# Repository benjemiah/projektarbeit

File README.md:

# projektarbeit

Git-Repo für die Projektarbeit des 6. Semesters

## Struktur

- **pcb**: KiCad-Projektdateien für die Platine des Retro-Terminals
  - **Gerber**: Gerber-Files der Platine
  - **eigenes.pretty**: Nicht-Standard Footprints/ Schaltzeichen für Bauteile
- **code**: Arduino-Code für die Atmega328P's des Retro-Terminals
- **presentation**
  - **website**: Website zur Präsentation des Projektseminars

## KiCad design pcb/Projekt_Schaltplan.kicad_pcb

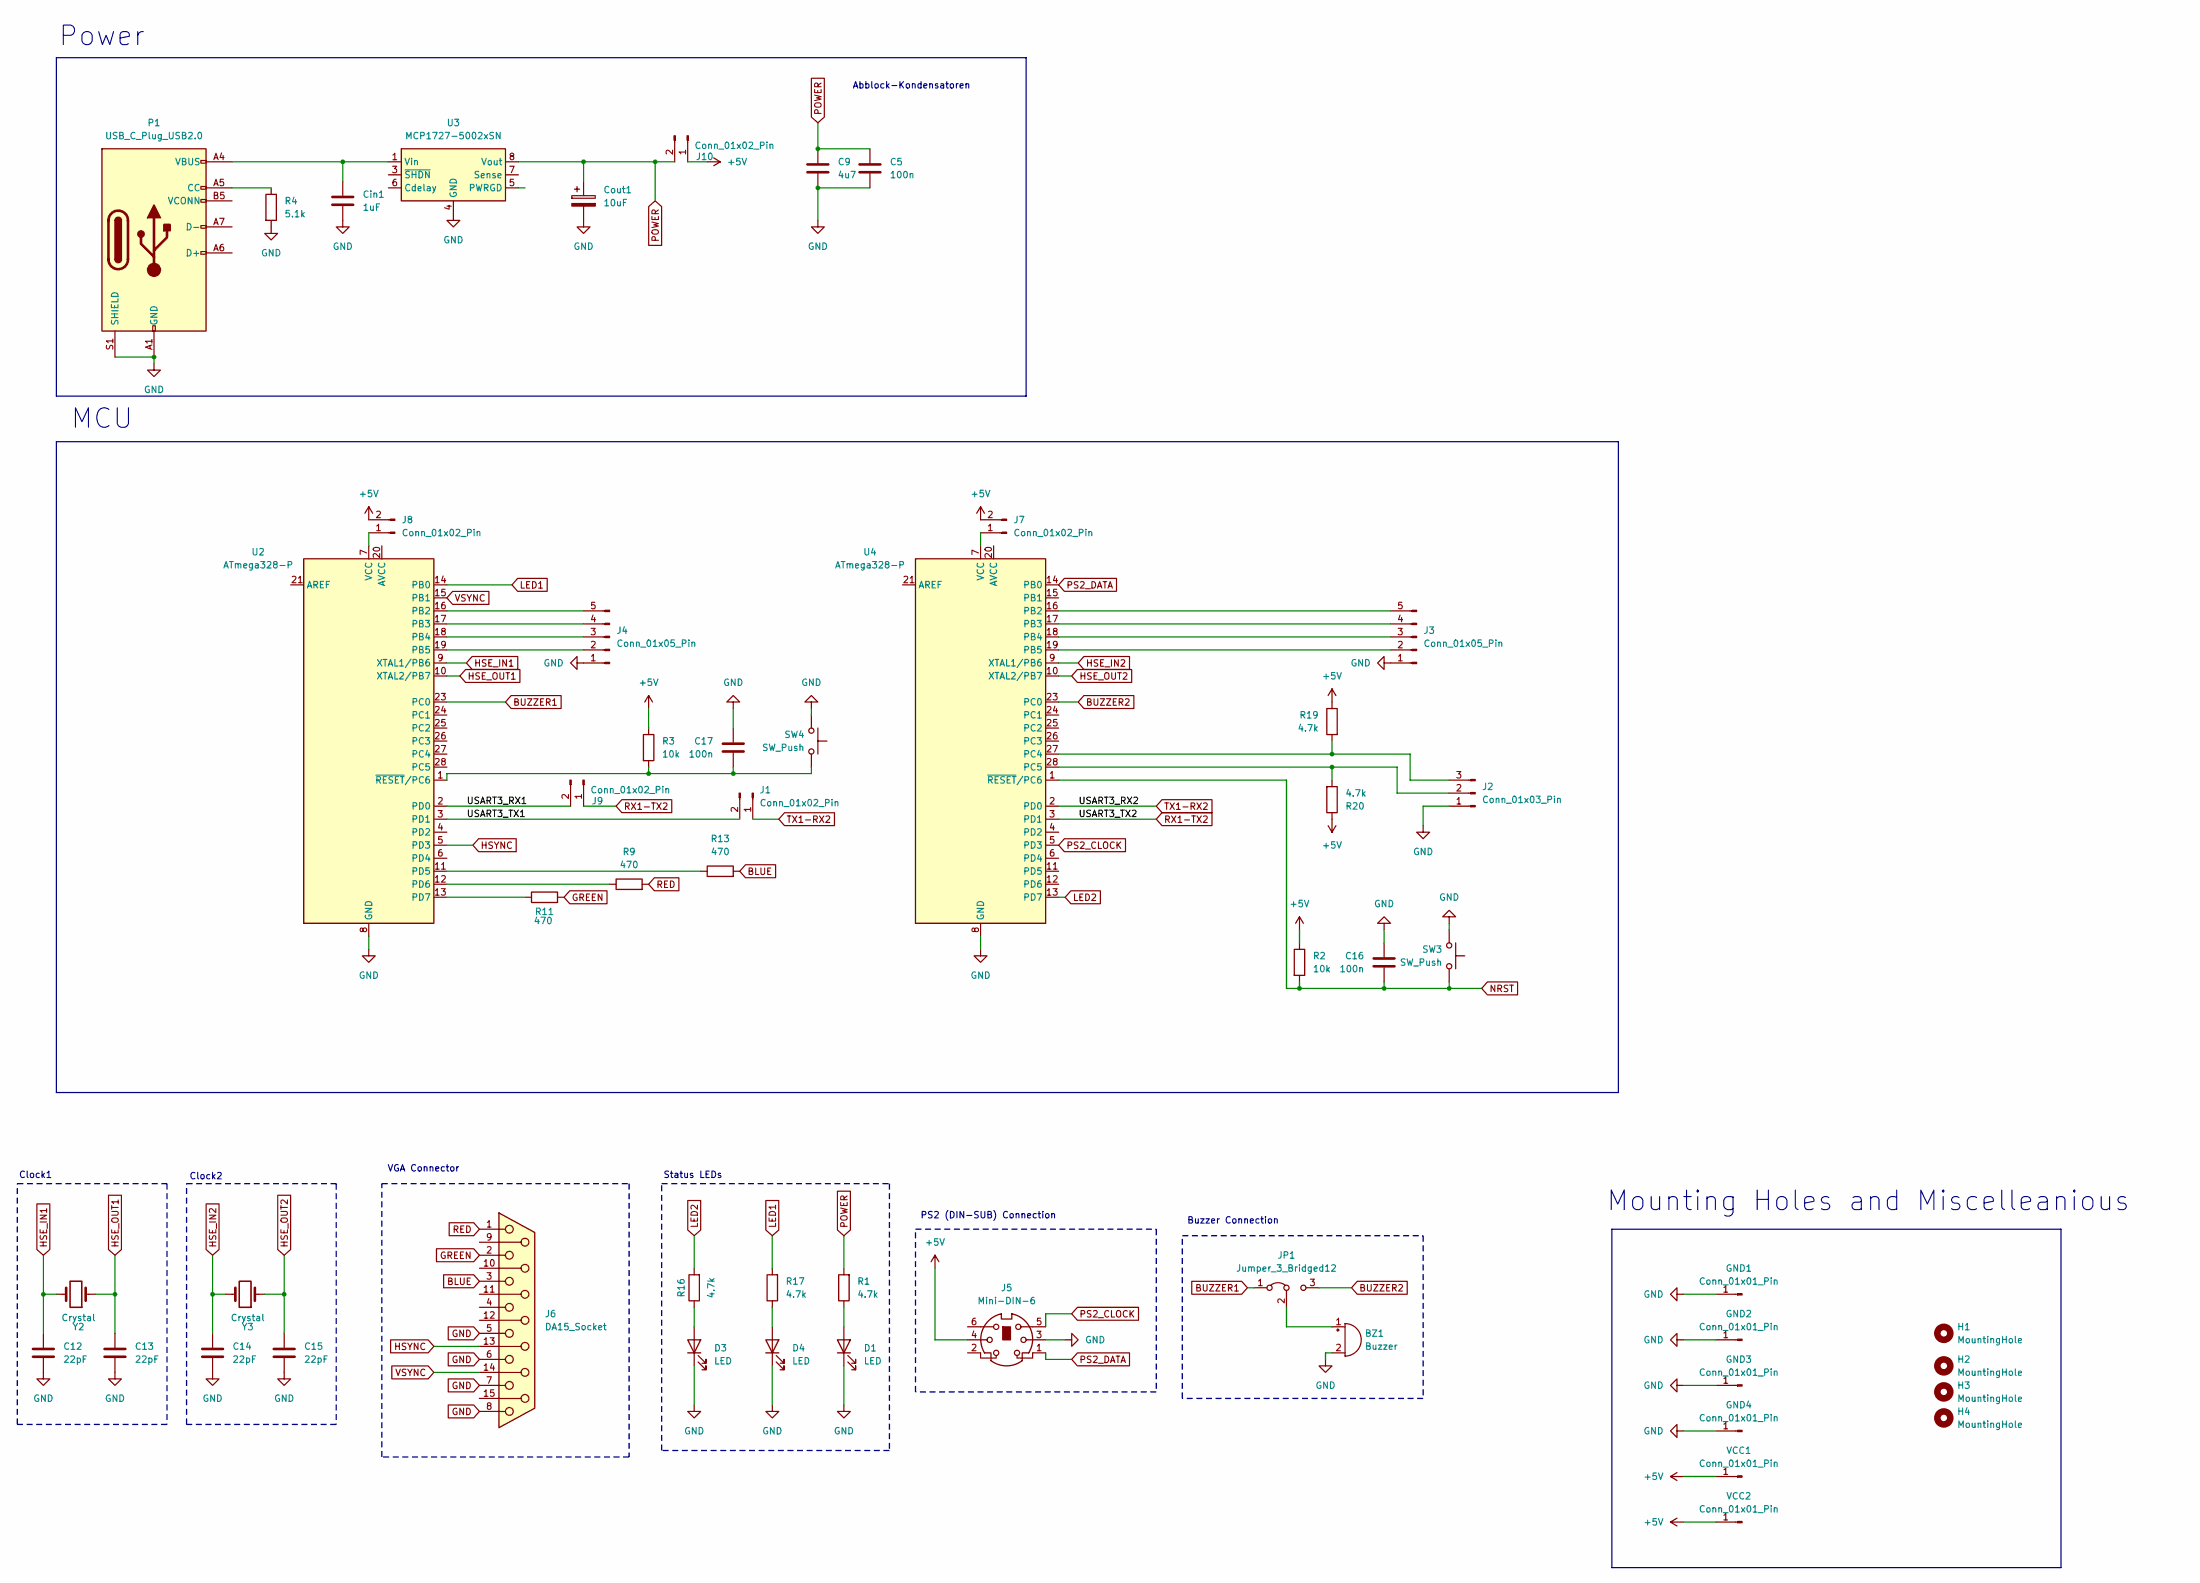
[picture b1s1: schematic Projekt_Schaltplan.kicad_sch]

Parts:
BZ1: Buzzer; Buzzer_12x9.5RM7.6
C5: 100n; C_0805_2012Metric_Pad1.18x1.45mm_HandSolder
C9: 4u7; C_0805_2012Metric_Pad1.18x1.45mm_HandSolder
C12, C13, C14, C15: 22pF; C_0805_2012Metric_Pad1.18x1.45mm_HandSolder
C16, C17: 100n; C_0603_1608Metric_Pad1.08x0.95mm_HandSolder
Cin1: 1uF; C_0805_2012Metric_Pad1.18x1.45mm_HandSolder
Cout1: 10uF; C_0805_2012Metric_Pad1.18x1.45mm_HandSolder
D1, D3, D4: LED; LED_0805_2012Metric_Pad1.15x1.40mm_HandSolder
GND1, GND2, GND3, GND4: Conn_01x01_Pin; TestPoint_THTPad_D2.0mm_Drill1.0mm
H1, H2, H3, H4: MountingHole; MountingHole_3.2mm_M3_DIN965_Pad
J1, J7, J8, J9, J10: Conn_01x02_Pin; PinHeader_1x02_P2.54mm_Vertical
J2: Conn_01x03_Pin; PinHeader_1x03_P2.54mm_Vertical
J3, J4: Conn_01x05_Pin; PinHeader_1x05_P2.54mm_Vertical
J5: Mini-DIN-6; ps2-buchse-6pin
J6: DA15_Socket; DSUB-15-HD_Socket_Vertical_P2.29x1.98mm_MountingHoles
JP1: Jumper_3_Bridged12; PinHeader_1x03_P2.54mm_Vertical
P1: USB_C_Plug_USB2.0; USB_C_Receptacle_GCT_USB4105-xx-A_16P_TopMnt_Horizontal
R1, R16, R17, R19, R20: 4.7k; R_0805_2012Metric_Pad1.20x1.40mm_HandSolder
R2, R3: 10k; R_0805_2012Metric_Pad1.20x1.40mm_HandSolder
R4: 5.1k; R_0805_2012Metric_Pad1.20x1.40mm_HandSolder
R9, R11, R13: 470; R_0805_2012Metric_Pad1.20x1.40mm_HandSolder
SW3, SW4: SW_Push; SW_PUSH_6mm
U2, U4: ATmega328-P; DIP-28_W7.62mm_Socket
U3: MCP1727-5002xSN; SOIC-8_3.9x4.9mm_P1.27mm
VCC1, VCC2: Conn_01x01_Pin; TestPoint_THTPad_D2.0mm_Drill1.0mm
Y2, Y3: Crystal; Crystal_HC49-U_Vertical

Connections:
+5V: J5.4, J7.2, J8.2, J10.1, R2.1, R3.1, R19.1, R20.1, VCC1.1, VCC2.1
/USART3_RX1: J9.2, U2.2 (PD0)
/USART3_TX1: J1.2, U2.3 (PD1)
BLUE: J6.3, R13.2
BUZZER1: JP1.1 (A), U2.23 (PC0)
BUZZER2: JP1.3 (B), U4.23 (PC0)
GND: BZ1.2 (-), C5.2, C9.2, C12.2, C13.2, C14.2, C15.2, C16.1, C17.1, Cin1.2, Cout1.2, D1.1 (K), D3.1 (K), D4.1 (K), GND1.1, GND2.1, GND3.1, GND4.1, J2.1, J3.1, J4.1, J5.3, J6.5, J6.6, J6.7, J6.8, P1.A1 (GND), P1.A12 (GND), P1.B1 (GND), P1.B12 (GND), P1.S1 (SHIELD), R4.2, SW3.2, SW4.2, U2.8 (GND), U2.22 (GND), U3.4 (GND), U4.8 (GND), U4.22 (GND)
GREEN: J6.2, R11.2
HSE_IN1: C12.1, U2.9 (XTAL1/PB6), Y2.2
HSE_IN2: C14.1, U4.9 (XTAL1/PB6), Y3.2
HSE_OUT1: C13.1, U2.10 (XTAL2/PB7), Y2.1
HSE_OUT2: C15.1, U4.10 (XTAL2/PB7), Y3.1
HSYNC: J6.13, U2.5 (PD3)
LED1: R17.2, U2.14 (PB0)
LED2: R16.2, U4.13 (PD7)
NRST: C16.2, R2.2, SW3.1, U4.1 (~RESET/PC6)
unnamed: BZ1.1 (+), JP1.2 (C)
unnamed: Cin1.1, P1.A4 (VBUS), P1.A9 (VBUS), P1.B4 (VBUS), P1.B9 (VBUS), U3.1 (Vin), U3.2 (Vin)
unnamed: D1.2 (A), R1.1
unnamed: D3.2 (A), R16.1
unnamed: D4.2 (A), R17.1
unnamed: J2.2, R20.2, U4.28 (PC5)
unnamed: J2.3, R19.2, U4.27 (PC4)
unnamed: J3.2, U4.19 (PB5)
unnamed: J3.3, U4.18 (PB4)
unnamed: J3.4, U4.17 (PB3)
unnamed: J3.5, U4.16 (PB2)
unnamed: J4.2, U2.19 (PB5)
unnamed: J4.3, U2.18 (PB4)
unnamed: J4.4, U2.17 (PB3)
unnamed: J4.5, U2.16 (PB2)
unnamed: J7.1, U4.7 (VCC)
unnamed: J8.1, U2.7 (VCC)
unnamed: P1.A5 (CC), R4.1
unnamed: R13.1, U2.11 (PD5)
unnamed: R9.1, U2.12 (PD6)
unnamed: R11.1, U2.13 (PD7)
unnamed: C17.2, R3.2, SW4.1, U2.1 (~RESET/PC6)
POWER: C5.1, C9.1, Cout1.1, J10.2, R1.2, U3.8 (Vout)
PS2_CLOCK: J5.5, U4.5 (PD3)
PS2_DATA: J5.1, U4.14 (PB0)
RED: J6.1, R9.2
RX1-TX2: J9.1, U4.3 (PD1)
TX1-RX2: J1.1, U4.2 (PD0)
VSYNC: J6.14, U2.15 (PB1)

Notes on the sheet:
Power
Clock1
PS2 (DIN-SUB) Connection
Clock2
Abblock-Kondensatoren
Buzzer Connection
MCU
Mounting Holes and Miscelleanious
Status LEDs
VGA Connector

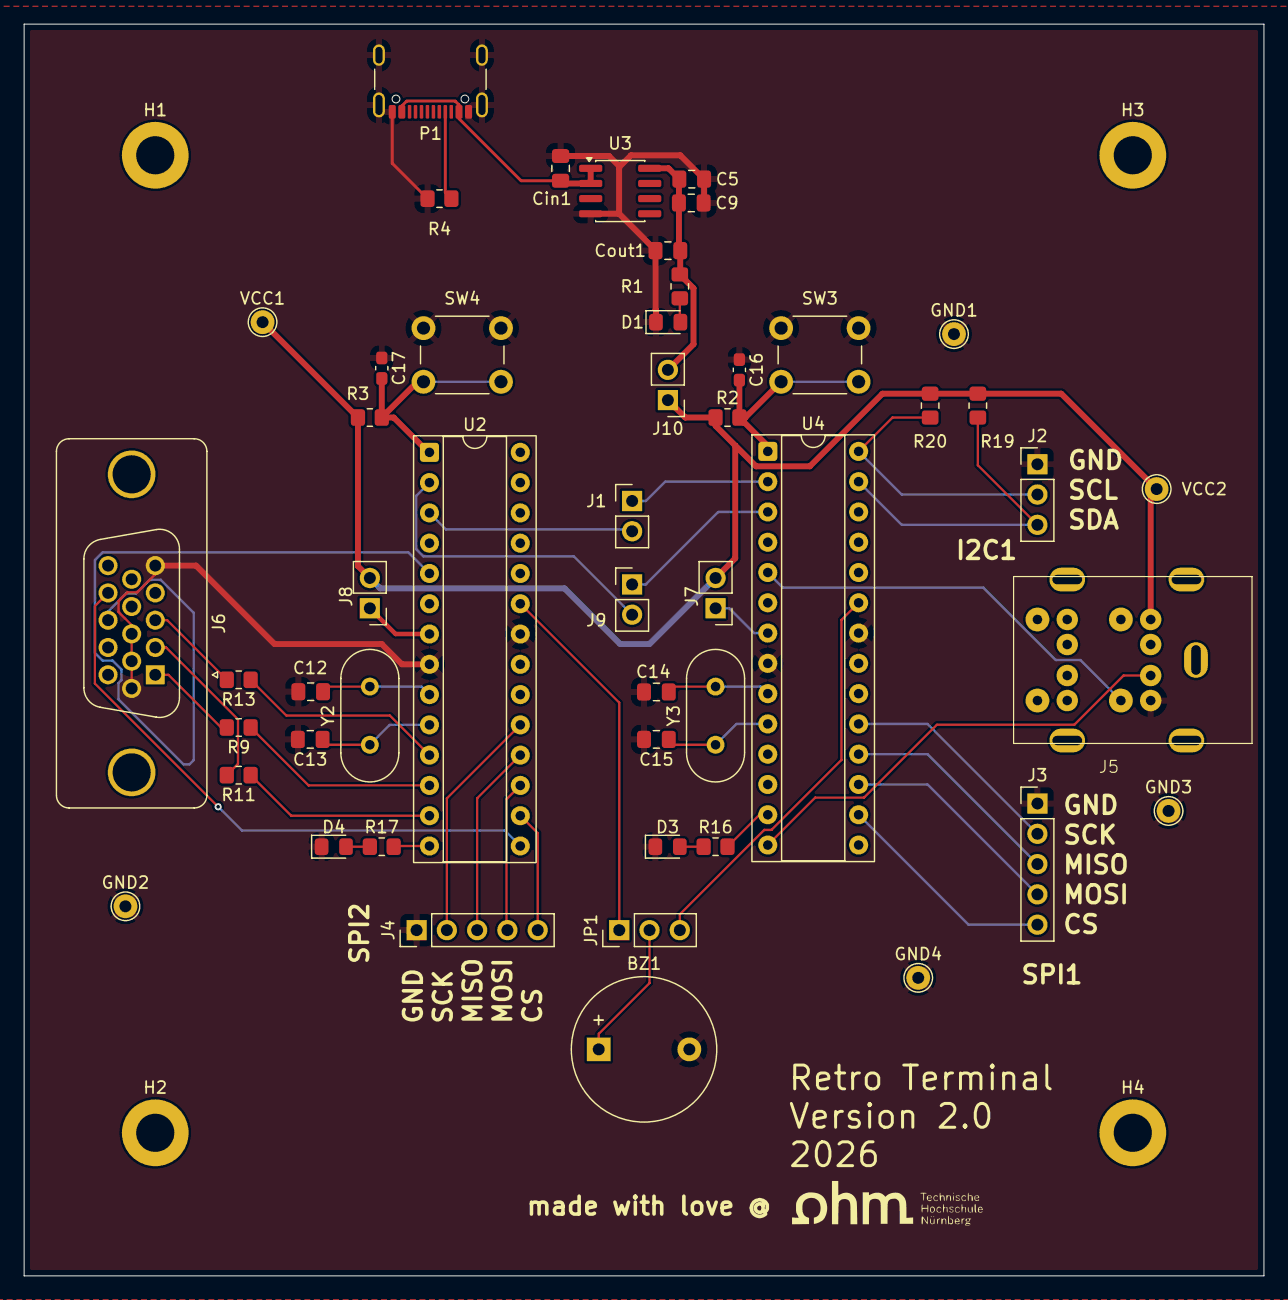
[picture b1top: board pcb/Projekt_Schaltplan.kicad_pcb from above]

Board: 2 copper layers, 104.0 x 105.0 mm, 54 parts (0 on the bottom side), 45 nets.

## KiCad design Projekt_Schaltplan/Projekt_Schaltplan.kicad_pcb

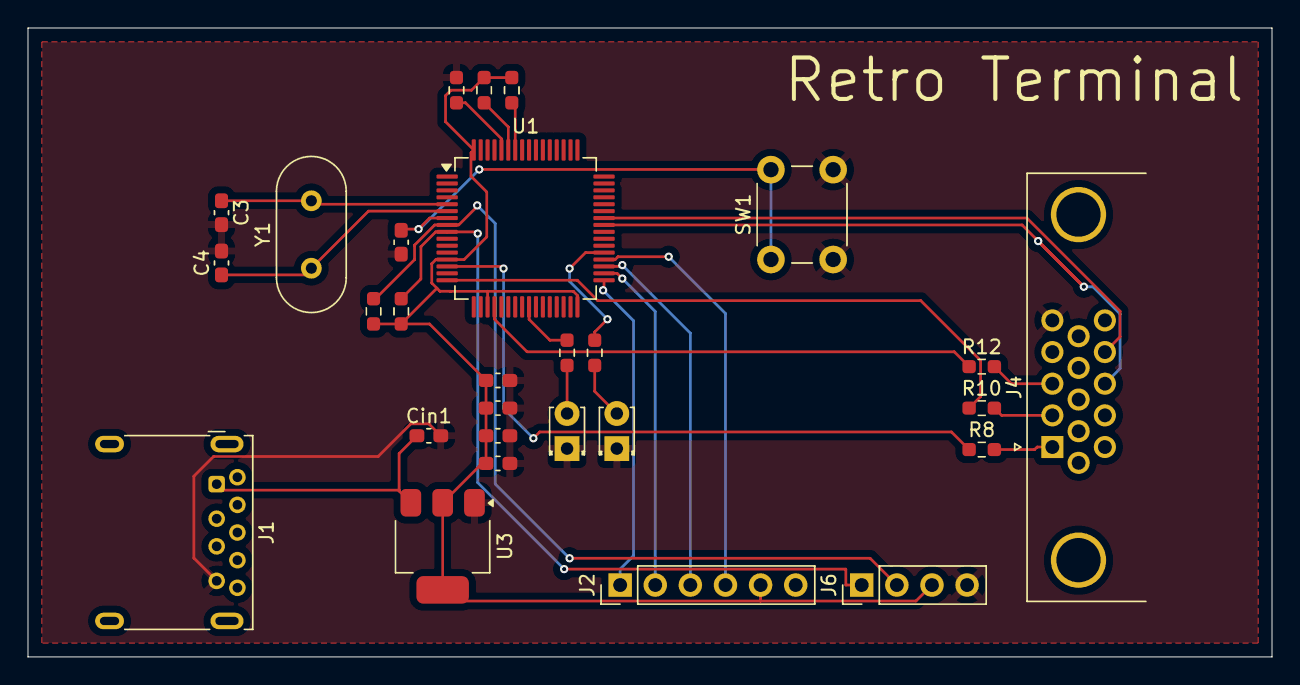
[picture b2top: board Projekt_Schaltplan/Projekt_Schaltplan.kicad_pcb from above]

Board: 2 copper layers, 90.0 x 45.5 mm, 28 parts (0 on the bottom side), 27 nets.

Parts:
C3, C4: 22pF; C_0603_1608Metric_Pad1.08x0.95mm_HandSolder
C5, C6, C10: 100n; C_0603_1608Metric_Pad1.08x0.95mm_HandSolder
C9: 4u7; C_0603_1608Metric_Pad1.08x0.95mm_HandSolder
Cin1: 1uF; C_0603_1608Metric_Pad1.08x0.95mm_HandSolder
Cout1: 2.2uF; C_0603_1608Metric_Pad1.08x0.95mm_HandSolder
D1: LED_red; LED_D1.8mm_W3.3mm_H2.4mm
D2: LED_green; LED_D1.8mm_W3.3mm_H2.4mm
J1: USB_A; USB3_A_Molex_48393-001
J2: Conn_01x06_Pin; PinHeader_1x06_P2.54mm_Vertical
J4: DA15_Socket; DSUB-15-HD_Pins_Horizontal_P2.29x1.90mm_EdgePinOffset3.03mm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
J6: Conn_01x04_Pin; PinHeader_1x04_P2.54mm_Vertical
R1, R2, R3, R4, R5: 4.7k; R_0603_1608Metric_Pad0.98x0.95mm_HandSolder
R6, R7: 200; R_0603_1608Metric_Pad0.98x0.95mm_HandSolder
R8, R10, R12: 470; R_0603_1608Metric_Pad0.98x0.95mm_HandSolder
SW1: SW_Push; SW_PUSH_6mm_H13mm
U1: STM32L476RCTx; LQFP-64_10x10mm_P0.5mm
U3: TLV76133DCY; SOT-223-3_TabPin2
Y1: Crystal; Crystal_HC49-U_Vertical

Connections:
+3.3V: C5.1, C6.1, C9.1, Cout1.1, J2.5, J6.3, R1.1, R2.1, R3.1, R4.1, U1.13 (VDDA), U1.19 (VDD), U1.32 (VDD), U1.64 (VDD), U3.2 (VO)
BLUE: J4.3, R12.2
GND: C3.2, C4.2, C5.2, C6.2, C9.2, C10.1, Cin1.2, Cout1.2, D1.1 (K), D2.1 (K), J1.4 (GND), J2.6, J4.5, J6.4, R5.1, SW1.2, U1.12 (VSSA), U1.18 (VSS), U1.31 (VSS), U1.47 (VSS), U1.63 (VSS), U3.1 (GND)
GREEN: J4.2, R10.2
HSE_IN: C3.1, U1.5 (PH0), Y1.2
HSE_OUT: C4.1, U1.6 (PH1), Y1.1
HSYNC: J4.13, U1.41 (PA8)
I2C1_SCL: J6.2, R3.2, U1.8 (PC0)
I2C1_SDA: J6.1, R4.2, U1.9 (PC1)
LED1: R6.2, U1.25 (PC5)
LED2: R7.2, U1.37 (PC6)
NRST: C10.2, SW1.1, U1.7 (NRST)
unnamed: D1.2 (A), R7.1
unnamed: D2.2 (A), R6.1
unnamed: Cin1.1, J1.1 (VBUS), U3.3 (VI)
unnamed: R5.2, U1.60 (BOOT0)
unnamed: R8.1, U1.14 (PA0)
unnamed: R10.1, U1.16 (PA2)
unnamed: R12.1, U1.20 (PA4)
unnamed: R1.2, U1.58 (PB6)
unnamed: R2.2, U1.59 (PB7)
RED: J4.1, R8.2
SPI2_CS: J2.1, U1.33 (PB12)
SPI2_MISO: J2.3, U1.35 (PB14)
SPI2_MOSI: J2.4, U1.36 (PB15)
SPI2_SCK: J2.2, U1.34 (PB13)
VSYNC: J4.14, U1.42 (PA9)

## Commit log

2025-04-26 Adding Markdown as Documentation for the whole Project
2025-04-26 adding readme for index.html
2025-04-26 adding markdown for installation
2025-04-26 adding module diagram
2025-04-26 adding file
2025-05-17 code that can display a filled screen with incredible timing problems
2025-05-24 adding pcb layout
2026-05-15 [feat] adding KICAD project and Gerber files
2026-05-15 [refactoring, feat] adding documentation and refactoring pcb annotation
2026-05-19 [feat] adding software docs
2026-05-19 [refactor] refactoring repo
2026-05-19 [feat] adding vga-driver for atmega328p #1
2026-05-20 [refactor] [feat] adding code for second atmega and refactoring repo
2026-05-20 [refactor] removing .odt
2026-05-20 [refactor] editing readme for readability
2026-05-20 [refactor] [feat] adding final documentation and refactoring
2026-05-20 [feat] adding render of pcb for visual representation
2026-05-20 [feat] adding final features for documentation
2026-05-21 [feat] adding final documentation
